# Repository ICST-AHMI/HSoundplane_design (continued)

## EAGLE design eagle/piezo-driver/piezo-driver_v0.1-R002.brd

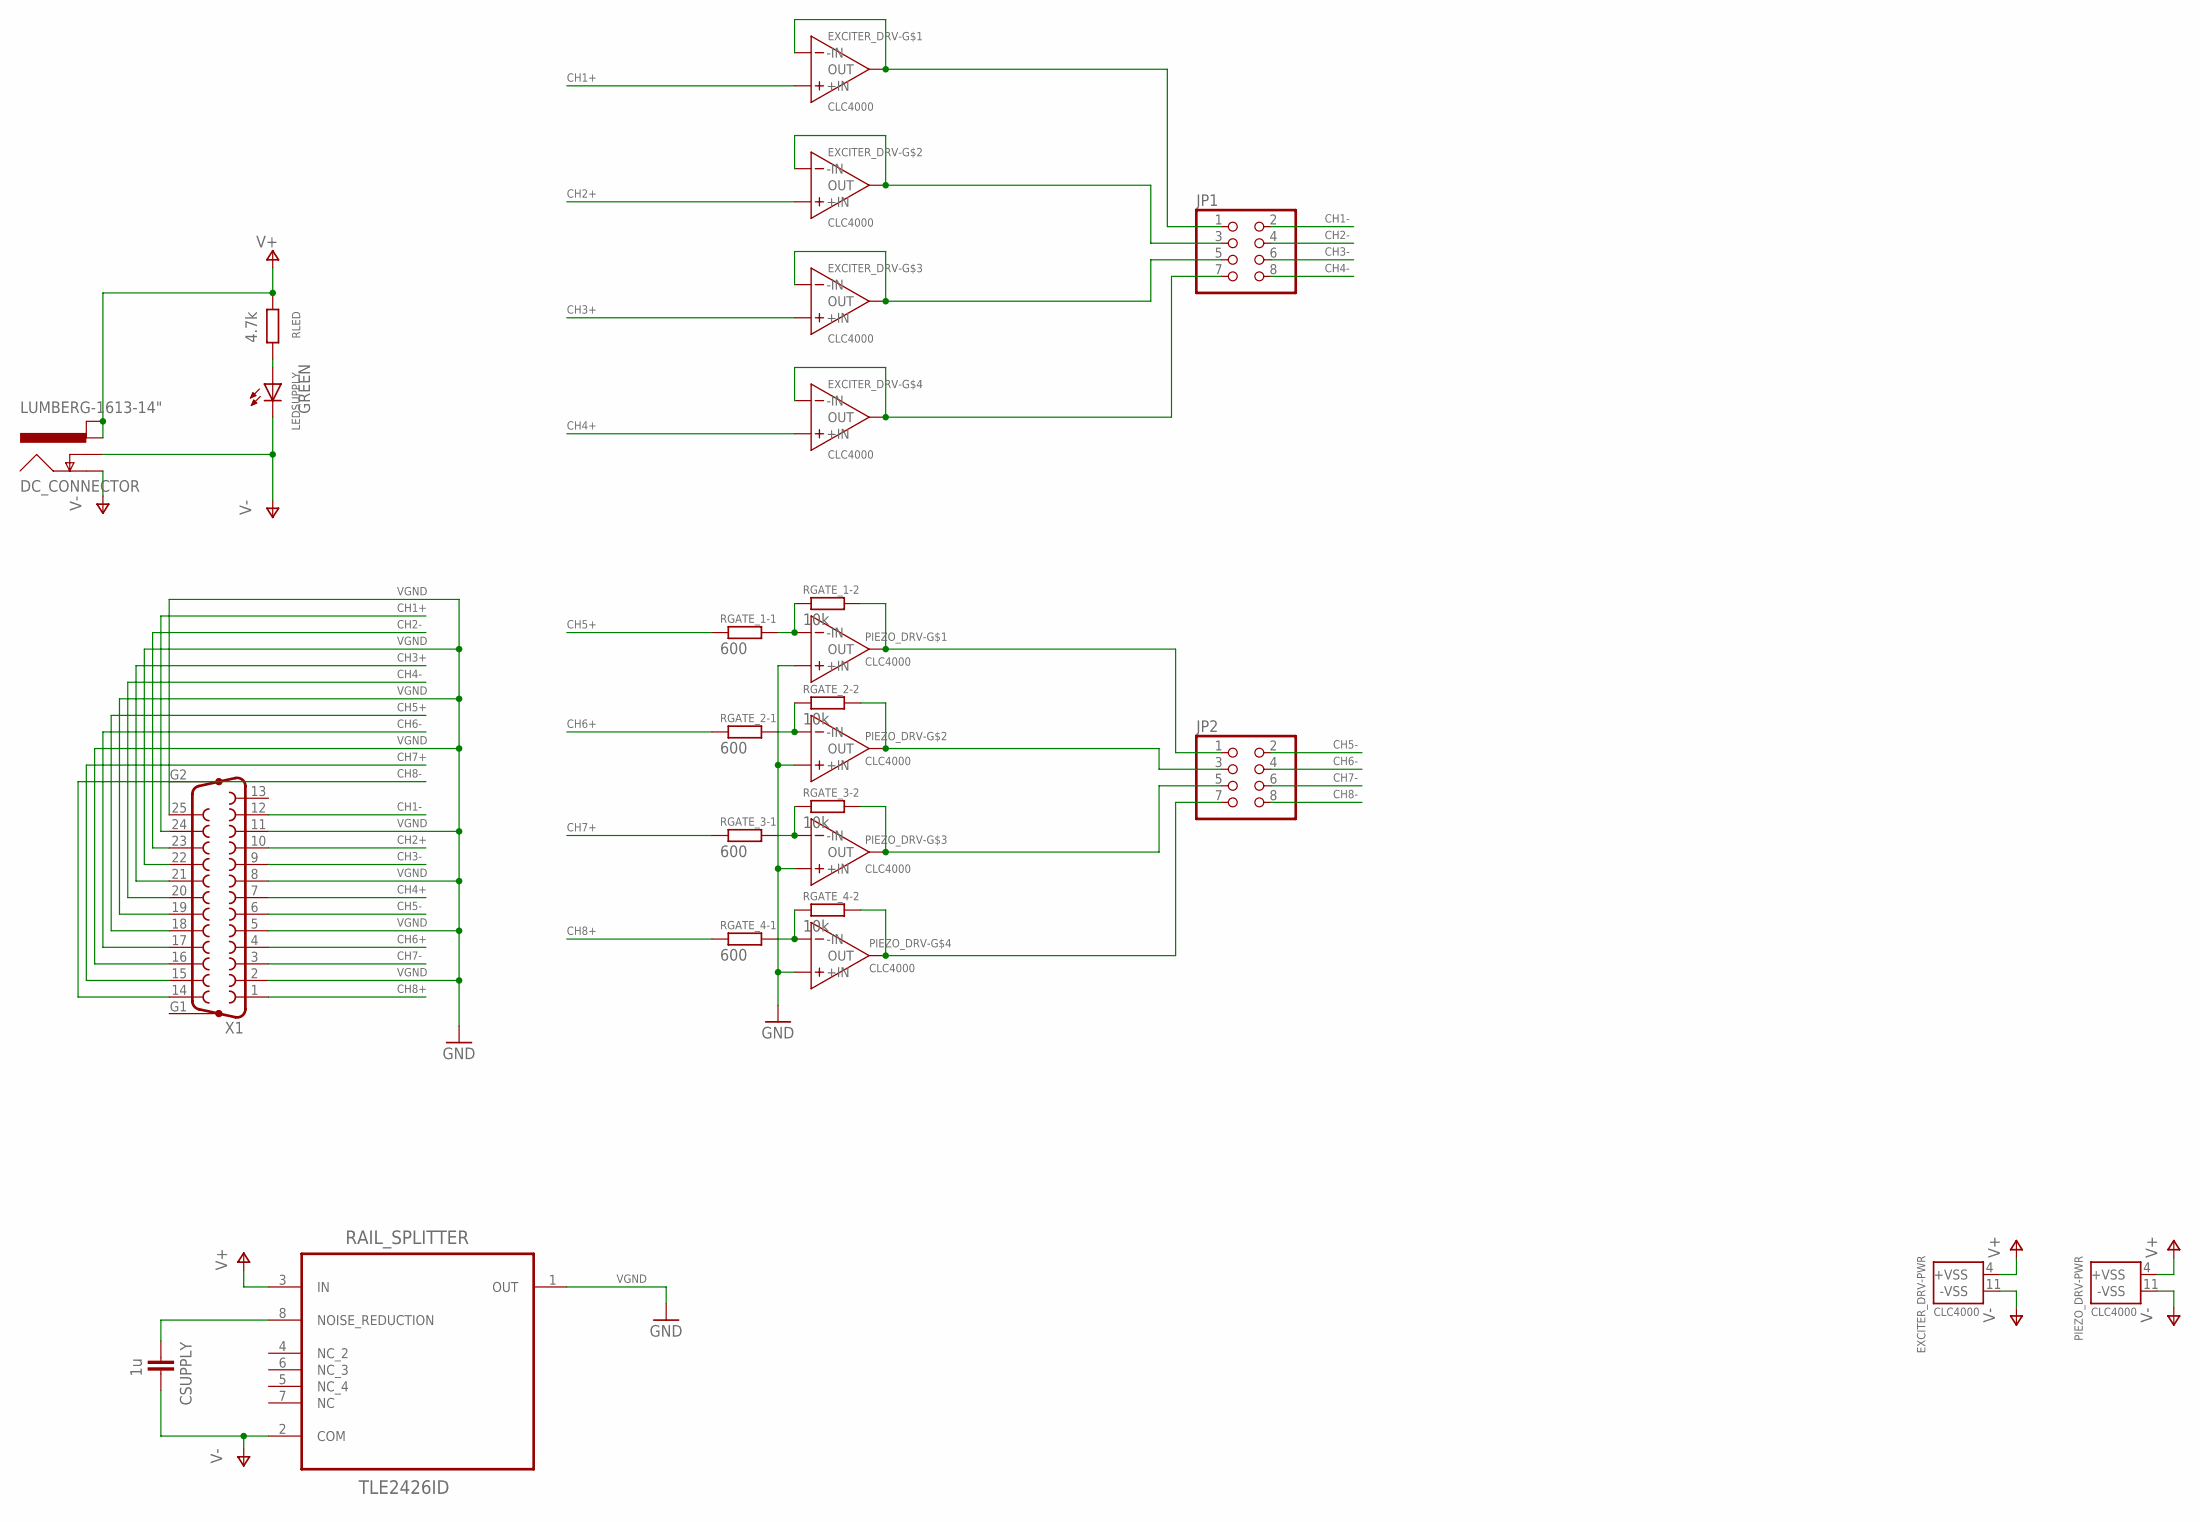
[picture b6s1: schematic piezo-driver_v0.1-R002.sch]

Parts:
CSUPPLY: 1u; C0603
DC_CONNECTOR: LUMBERG-1613-14"; LUMBERG-1613_14
EXCITER_DRV: CLC4000; SOIC-14
JP1, JP2: PINHD-2X4/90; 2X04/90
LEDSUPPLY: GREEN; LED3MM
PIEZO_DRV: CLC4000; SOIC-14
RAIL_SPLITTER: TLE2426ID; SOIC127P600X175-8N
RGATE_1-1, RGATE_2-1, RGATE_3-1, RGATE_4-1: 600; R0805
RGATE_1-2, RGATE_2-2, RGATE_3-2, RGATE_4-2: 10k; R0805
RLED: 4.7k; R0805
X1: F25HP

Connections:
CH1+: EXCITER_DRV.3 (+IN), X1.24
CH1-: JP1.2, X1.12
CH2+: EXCITER_DRV.5 (+IN), X1.10
CH2-: JP1.4, X1.23
CH3+: EXCITER_DRV.10 (+IN), X1.21
CH3-: JP1.6, X1.9
CH4+: EXCITER_DRV.12 (+IN), X1.7
CH4-: JP1.8, X1.20
CH5+: RGATE_1-1.1, X1.18
CH5-: JP2.2, X1.6
CH6+: RGATE_2-1.1, X1.4
CH6-: JP2.4, X1.17
CH7+: RGATE_3-1.1, X1.15
CH7-: JP2.6, X1.3
CH8+: RGATE_4-1.1, X1.1
CH8-: JP2.8, X1.14
unnamed: EXCITER_DRV.1 (OUT), EXCITER_DRV.2 (-IN), JP1.1
unnamed: EXCITER_DRV.6 (-IN), EXCITER_DRV.7 (OUT), JP1.3
unnamed: EXCITER_DRV.8 (OUT), EXCITER_DRV.9 (-IN), JP1.5
unnamed: EXCITER_DRV.13 (-IN), EXCITER_DRV.14 (OUT), JP1.7
unnamed: CSUPPLY.1, RAIL_SPLITTER.8 (NOISE_REDUCTION)
unnamed: PIEZO_DRV.2 (-IN), RGATE_1-1.2, RGATE_1-2.1
unnamed: JP2.1, PIEZO_DRV.1 (OUT), RGATE_1-2.2
unnamed: PIEZO_DRV.6 (-IN), RGATE_2-1.2, RGATE_2-2.1
unnamed: JP2.3, PIEZO_DRV.7 (OUT), RGATE_2-2.2
unnamed: PIEZO_DRV.9 (-IN), RGATE_3-1.2, RGATE_3-2.1
unnamed: JP2.5, PIEZO_DRV.8 (OUT), RGATE_3-2.2
unnamed: PIEZO_DRV.13 (-IN), RGATE_4-1.2, RGATE_4-2.1
unnamed: JP2.7, PIEZO_DRV.14 (OUT), RGATE_4-2.2
unnamed: LEDSUPPLY.A, RLED.1
V+: DC_CONNECTOR.3 (PWR_1), DC_CONNECTOR.4 (PWR_2), EXCITER_DRV.4 (+VSS), PIEZO_DRV.4 (+VSS), RAIL_SPLITTER.3 (IN), RLED.2
V-: CSUPPLY.2, DC_CONNECTOR.1 (GND), DC_CONNECTOR.2 (GND_INS), EXCITER_DRV.11 (-VSS), LEDSUPPLY.K (C), PIEZO_DRV.11 (-VSS), RAIL_SPLITTER.2 (COM)
VGND: PIEZO_DRV.3 (+IN), PIEZO_DRV.5 (+IN), PIEZO_DRV.10 (+IN), PIEZO_DRV.12 (+IN), RAIL_SPLITTER.1 (OUT), X1.2, X1.5, X1.8, X1.11, X1.16, X1.19, X1.22, X1.25

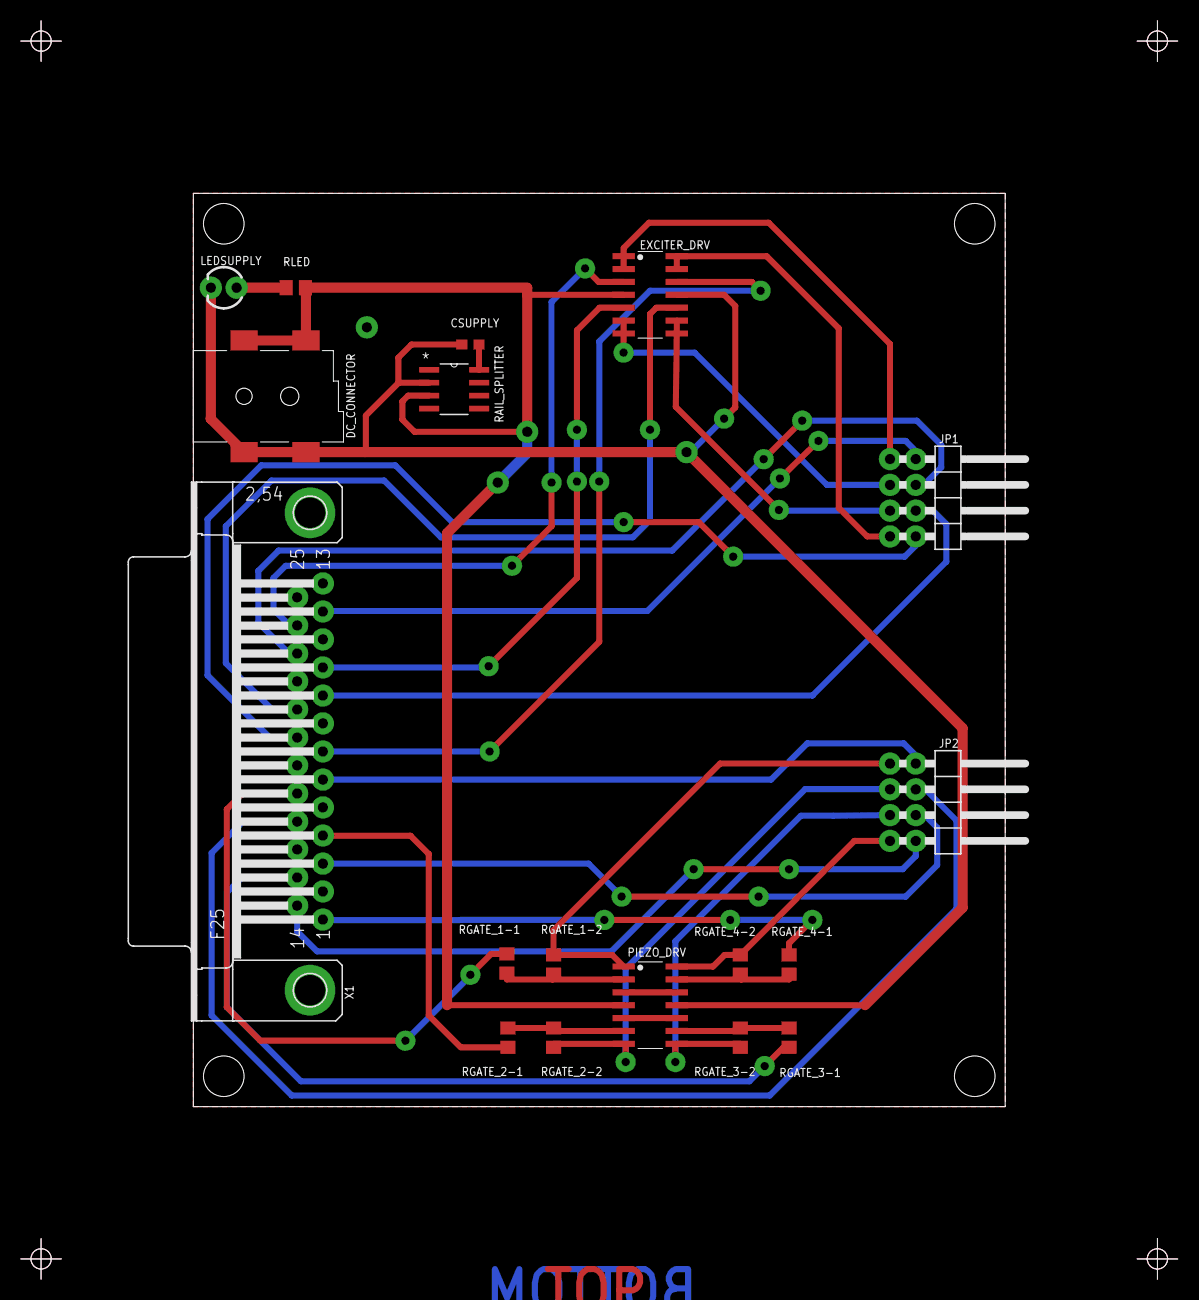
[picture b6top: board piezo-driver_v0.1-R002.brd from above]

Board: 2 copper layers, 80.0 x 90.0 mm, 18 parts (0 on the bottom side), 33 nets.

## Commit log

2015-09-14 added blender files
2015-09-16 tiny changes
2015-09-21 added foil support object
2016-02-24 added design for testing table so I can interact with the HSoundplane while it is upside down and with the guts open.
2016-11-30 Computerwechsel-Commit
